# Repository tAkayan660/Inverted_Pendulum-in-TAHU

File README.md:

# Inverted_Pendulum-in-TAHU

## 機能
1. ロボット本体を倒立振子する
2. マイコンはArduino Megaを使用
3. 姿勢制御にIMU（MPU-6050）を使用

## 動画

倒立        https://youtu.be/ehn2ii576s0?t=45s

重心下げ    https://youtu.be/hFfJ6d6ZRYU

再生リスト　https://www.youtube.com/playlist?list=PLqcSOQa__YqBw24QBU1EO53jK8HO_nGts

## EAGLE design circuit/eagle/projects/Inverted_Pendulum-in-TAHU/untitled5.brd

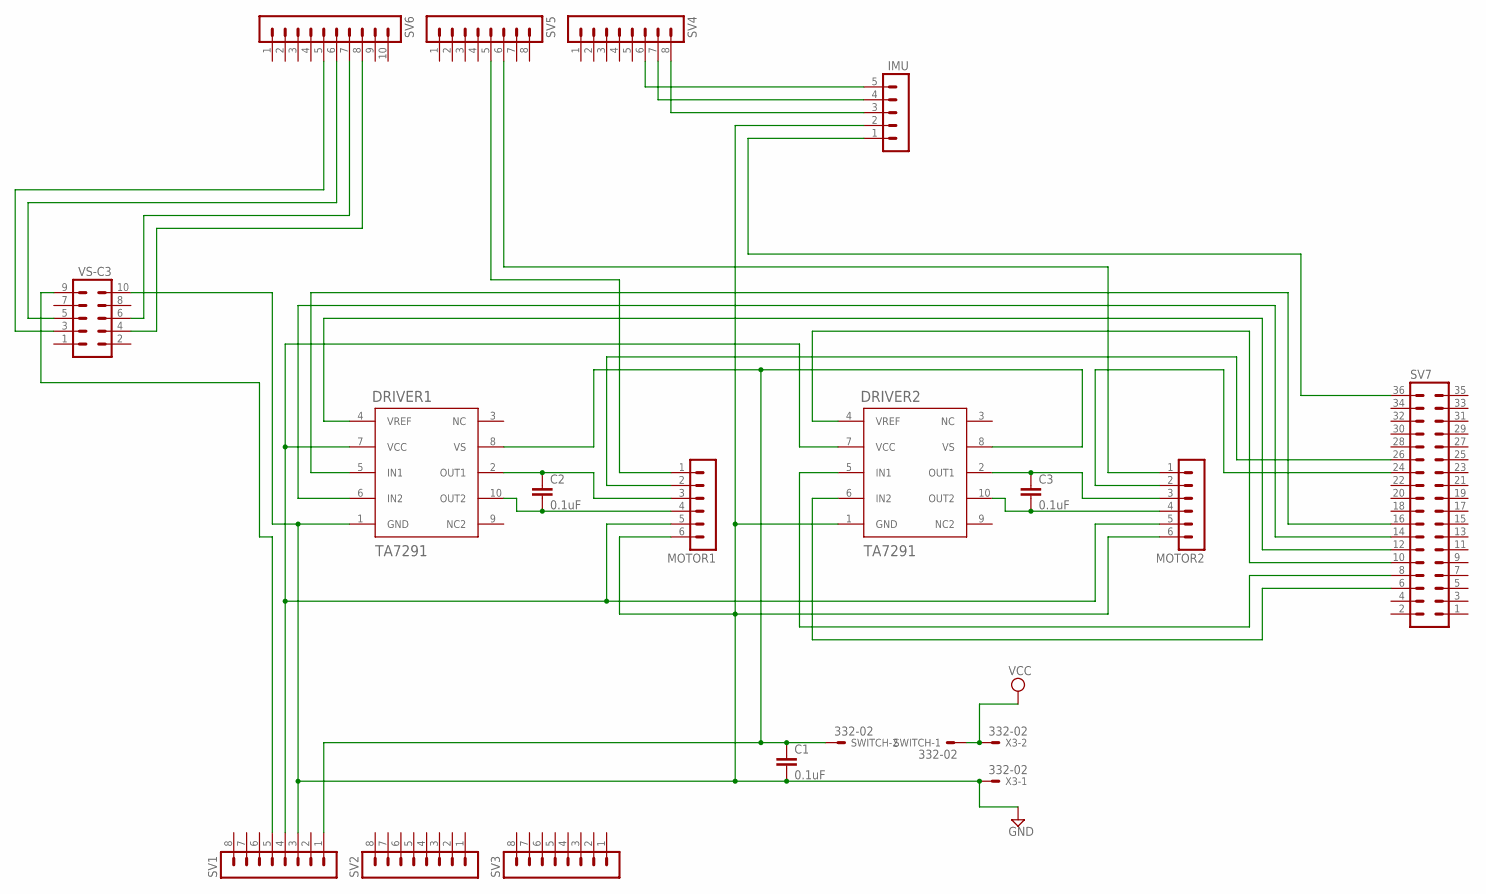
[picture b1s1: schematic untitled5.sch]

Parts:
C1, C2, C3: 0.1uF; C5B2.5
DRIVER1, DRIVER2: TA7291; HSIP10
IMU: MA05-1
MOTOR1, MOTOR2: MA06-1
SV1, SV2, SV3, SV4, SV5: MA08-1
SV6: MA10-1
SV7: MA18-2
SWITCH: 332-02
VS-C3: MA05-2
X3: 332-02

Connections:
ENCODER: IMU.5, SV4.6
GND: C1.2, DRIVER1.1 (GND), DRIVER2.1 (GND), IMU.2, MOTOR1.6, MOTOR2.6, SV1.3, VS-C3.10, X3.1
unnamed: C2.1, DRIVER1.2 (OUT1), MOTOR1.3
unnamed: C2.2, DRIVER1.10 (OUT2), MOTOR1.4
unnamed: C3.1, DRIVER2.2 (OUT1), MOTOR2.3
unnamed: C3.2, DRIVER2.10 (OUT2), MOTOR2.4
unnamed: IMU.1, SV7.36
unnamed: MOTOR2.1, SV5.6
unnamed: DRIVER1.7 (VCC), DRIVER2.7 (VCC), MOTOR1.5, MOTOR2.5, SV1.4
unnamed: IMU.3, SV4.8
unnamed: IMU.4, SV4.7
unnamed: C1.1, DRIVER1.8 (VS), DRIVER2.8 (VS), SV1.1, SWITCH.2
unnamed: DRIVER2.4 (VREF), SV7.10
unnamed: DRIVER1.5 (IN1), SV7.16
unnamed: MOTOR1.1, SV5.5
unnamed: MOTOR1.2, SV7.26
unnamed: MOTOR2.2, SV7.24
unnamed: DRIVER1.6 (IN2), SV7.14
unnamed: DRIVER2.5 (IN1), SV7.8
unnamed: DRIVER2.6 (IN2), SV7.6
unnamed: SV1.5, VS-C3.9
unnamed: SV6.6, VS-C3.5
unnamed: SV6.5, VS-C3.3
unnamed: SV6.8, VS-C3.4
unnamed: SV6.7, VS-C3.6
unnamed: DRIVER1.4 (VREF), SV7.12
VCC: SWITCH.1, X3.2

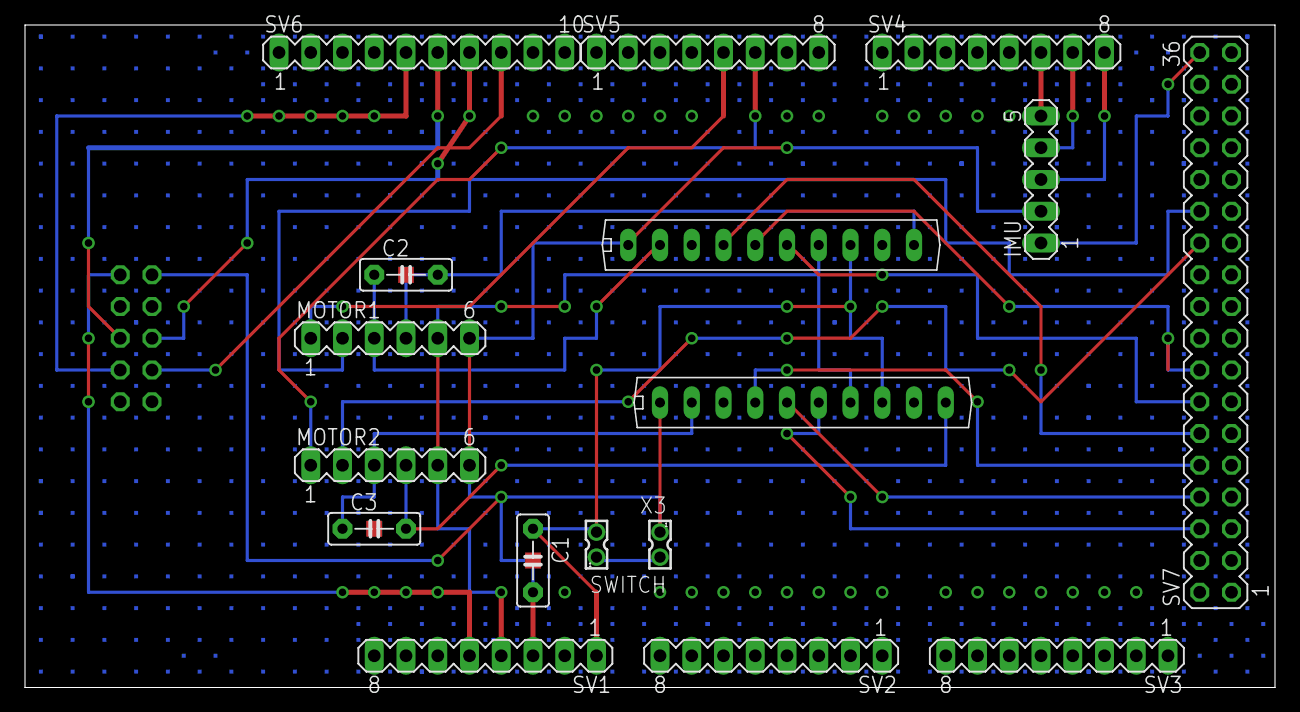
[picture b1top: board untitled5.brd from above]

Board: 2 copper layers, 100.0 x 53.0 mm, 18 parts (1 on the bottom side), 27 nets.

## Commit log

2016-07-04 add MPU6050_sample
2016-07-04 ライブラリの作成
2016-07-04 samples内の整理＆説明追加
2016-07-07 add circuit
2016-07-07 Update circuit
2016-07-25 2016/07/25
2016-07-29 add 回路の完成形＆スライド
